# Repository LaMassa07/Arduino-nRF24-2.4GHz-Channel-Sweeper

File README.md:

# Arduino-nRF24-2.4GHz-Channel-Sweeper   
Arduino project using an nRF24L01 to generate a constant carrier and perform a 2.4 GHz channel sweep for RF testing and experimentation purposes.

<br>

## 📌 Features
- **Generate** a constant RF carrier using nRF24L01
- **Sweep** across 2.4 GHz channels
- **Target** BLE advertising and data channels
- **Button‑controlled** transmission with LED status indicator
- **Configurable** channel timing and power level

<br>

## ⚙️ Setup
- First, be sure to have the <a href="https://www.arduino.cc/en/software/">Arduino IDE</a> at the last version

### Libraries
Go to `Sketch` → `Include Library` → `Add .ZIP Library` and install:
- **RF24** by *TMRh20* from <a href="https://github.com/tmrh20/RF24">here</a>

<br>

## 🛠️ Installing the code
Open the *code.ino* file with the IDE.
Before uploading it, you can edit the button and led pins.

When you are ready, click **Upload**

<br>

## 🔌 Build the circuit
### Materials:
- ARDUINO board *(I used ARDUINO Nano, but you can choose your ARDUINO, but be sure to use the right SPI pins)*
- 1 x buttons
- 1 x 220Ω resistors
- 1 x led
- 1 x nRF24l01+PA+LNA rf module
- 1 x 47uF capacitor

### Schematic

<br>
<br>

## 🖥️ Use
> ⚠️ **USE THIS ONLY IN A CONTROLLED ENVIRONMENT.**  
> This project is intended purely for *RF experimentation, learning, and demonstration purposes*.  
> Do not use near critical devices, production Wi-Fi, or Bluetooth networks.

<br>
<br>
<br>

## 📄 License

This project is released under the **MIT License**.  
See [LICENSE](./LICENSE) for details.

<br>

## 🙌 Credits
Inspired by the work of <a href="https://github.com/SecureTechware">**@SecureTechware**</a>, so consider taking a look at his original project.
<br>
<br>

Find Me on:

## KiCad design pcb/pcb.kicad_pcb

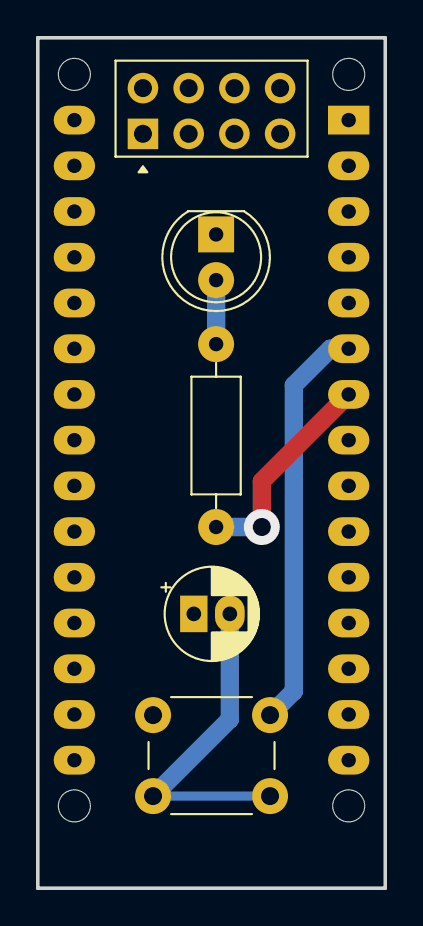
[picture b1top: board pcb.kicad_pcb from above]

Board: 2 copper layers, 19.3 x 47.2 mm, 6 parts (1 on the bottom side), 10 nets.

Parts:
A2: Arduino Nano; Arduino_Nano_WithMountingHoles
C2: 10uF; CP_Radial_D5.0mm_P2.00mm
L1: LED; LED_D5.0mm
OK1: P_1; SW_PUSH_6mm_H9.5mm
R1: 220; R_Axial_DIN0207_L6.3mm_D2.5mm_P10.16mm_Horizontal
U1: NRF24; nRF24L01_Breakout

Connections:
/BUTTON: A2.6 (D3), OK1.1
/CE: A2.12 (D9), U1.3 (CE)
/CSN: A2.13 (D10), U1.4 (~CSN)
/LED: A2.7 (D4), R1.2
/MISO: A2.15 (D12), U1.7 (MISO)
/MOSI: A2.14 (D11), U1.6 (MOSI)
/SCK: A2.16 (D13), U1.5 (SCK)
GND: A2.4 (GND), A2.29 (GND), C2.2, L1.1 (K), OK1.2, U1.1 (GND)
unnamed: L1.2 (A), R1.1
VCC: A2.17 (3V3), C2.1, U1.2 (VCC)
